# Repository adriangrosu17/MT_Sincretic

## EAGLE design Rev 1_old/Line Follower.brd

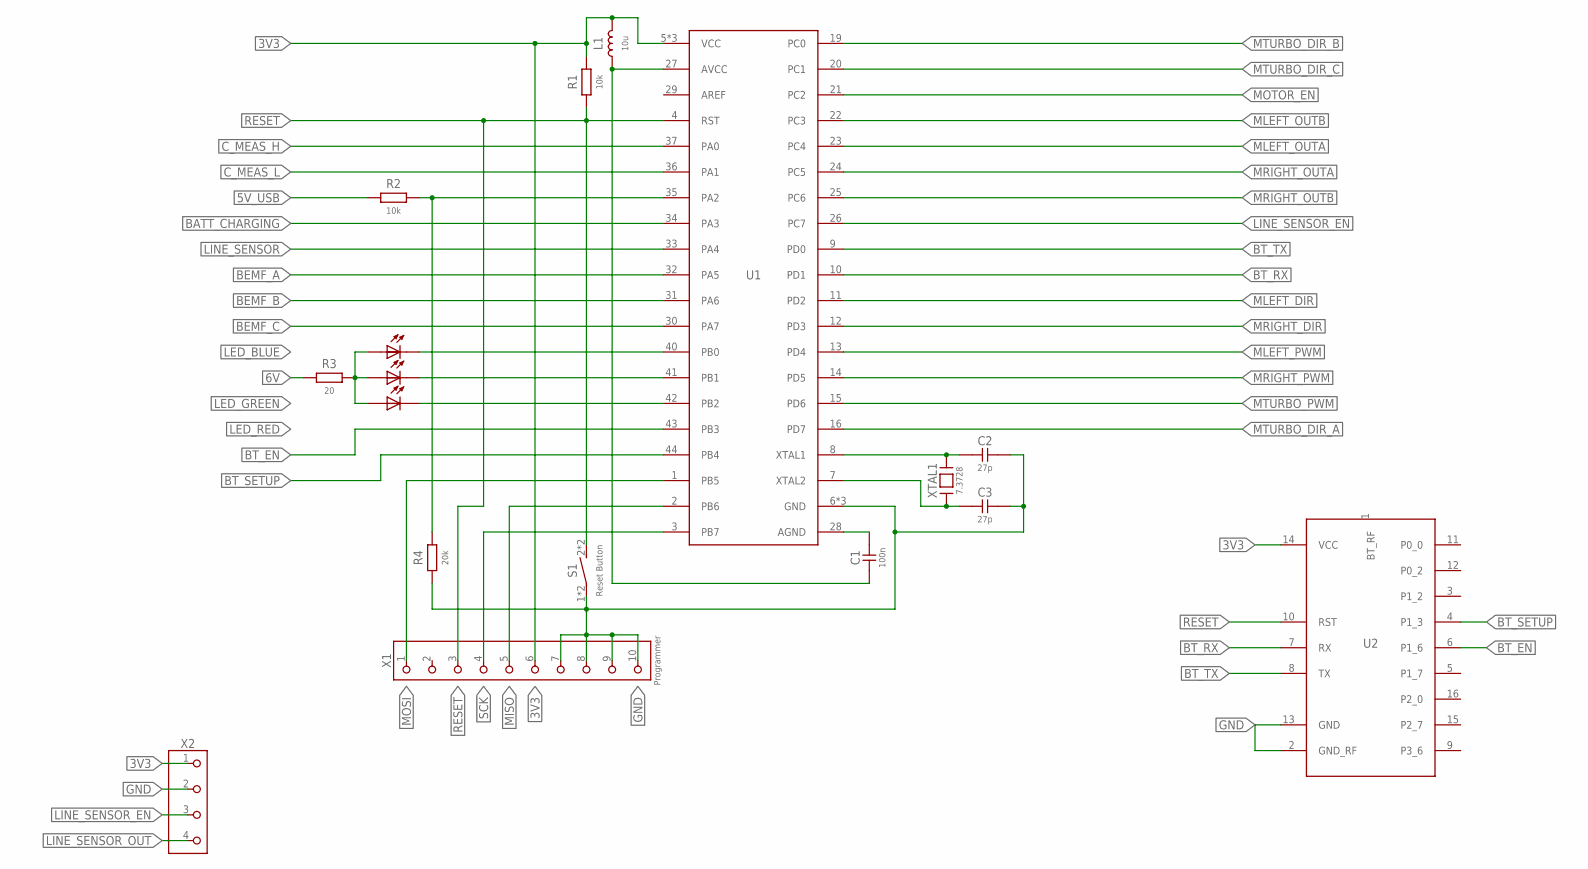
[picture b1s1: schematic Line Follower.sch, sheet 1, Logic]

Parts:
C1: 100n; SMD_1206
C2, C3: 27p; SMD_1206
D1: RGB_LEDOSTCXBSEC1E; OSTCXBSEC1E
L1: 10u; SMD_1206
R1, R2: 10k; SMD_1206
R3: 20; SMD_1206
R4: 20k; SMD_1206
S1: Reset Button; SCHURTER_BUTTON
U1: ATMEGA1284TQFP; TQFP-44
U2: RN4871
X1: Programmer; MALE_1WAY_2X5
X2: CONNECTOR_4PINMALE_PIN_1X4; MALE_PIN_1X4
XTAL1: 7.3728; SMD_OSCILLATOR

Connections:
3V3: L1.2, R1.2, U1.5 (VCC), U1.17 (VCC), U1.38 (VCC), U2.14 (VCC), X1.6, X2.1; also elsewhere on the board
5V_USB: R2.1; also elsewhere on the board
6V: R3.2; also elsewhere on the board
AVCC: C1.1, L1.1, U1.27 (AVCC)
BATT_CHARGING: U1.34 (PA3); also elsewhere on the board
BEMF_A: U1.32 (PA5); also elsewhere on the board
BEMF_B: U1.31 (PA6); also elsewhere on the board
BEMF_C: U1.30 (PA7); also elsewhere on the board
BT_EN: U1.43 (PB3), U2.6 (P1_6)
BT_RX: U1.10 (PD1), U2.7 (RX)
BT_SETUP: U1.44 (PB4), U2.4 (P1_3)
BT_TX: U1.9 (PD0), U2.8 (TX)
C_MEAS_H: U1.37 (PA0); also elsewhere on the board
C_MEAS_L: U1.36 (PA1); also elsewhere on the board
GND: C2.1, C3.1, R4.1, S1.1, S1.3, U1.6 (GND), U1.18 (GND), U1.39 (GND), U2.2 (GND_RF), U2.13 (GND), X1.7, X1.8, X1.9, X1.10, X2.2; also elsewhere on the board
LED_BLUE: D1.3 (K), U1.40 (PB0)
LED_GREEN: D1.1 (K), U1.41 (PB1)
LED_RED: D1.2 (K), U1.42 (PB2)
LINE_SENSOR: U1.33 (PA4)
LINE_SENSOR_EN: U1.26 (PC7), X2.3; also elsewhere on the board
LINE_SENSOR_OUT: X2.4; also elsewhere on the board
MISO: U1.2 (PB6), X1.5
MLEFT_DIR: U1.11 (PD2); also elsewhere on the board
MLEFT_OUTA: U1.23 (PC4); also elsewhere on the board
MLEFT_OUTB: U1.22 (PC3); also elsewhere on the board
MLEFT_PWM: U1.13 (PD4); also elsewhere on the board
MOSI: U1.1 (PB5), X1.1
MOTOR_EN: U1.21 (PC2); also elsewhere on the board
MRIGHT_DIR: U1.12 (PD3); also elsewhere on the board
MRIGHT_OUTA: U1.24 (PC5); also elsewhere on the board
MRIGHT_OUTB: U1.25 (PC6); also elsewhere on the board
MRIGHT_PWM: U1.14 (PD5); also elsewhere on the board
MTURBO_DIR_A: U1.16 (PD7); also elsewhere on the board
MTURBO_DIR_B: U1.19 (PC0); also elsewhere on the board
MTURBO_DIR_C: U1.20 (PC1); also elsewhere on the board
MTURBO_PWM: U1.15 (PD6); also elsewhere on the board
unnamed: C3.2, U1.7 (XTAL2), XTAL1.1
unnamed: C2.2, U1.8 (XTAL1), XTAL1.2
unnamed: C1.2, U1.28 (AGND)
unnamed: D1.4 (A), D1.5 (A), D1.6 (A), D1.PAD (A), R3.1
RESET: R1.1, S1.2 (S), S1.4 (S), U1.4 (RST), U2.10 (RST), X1.3
SCK: U1.3 (PB7), X1.4
USB_CONNECTED: R2.2, R4.2, U1.35 (PA2)

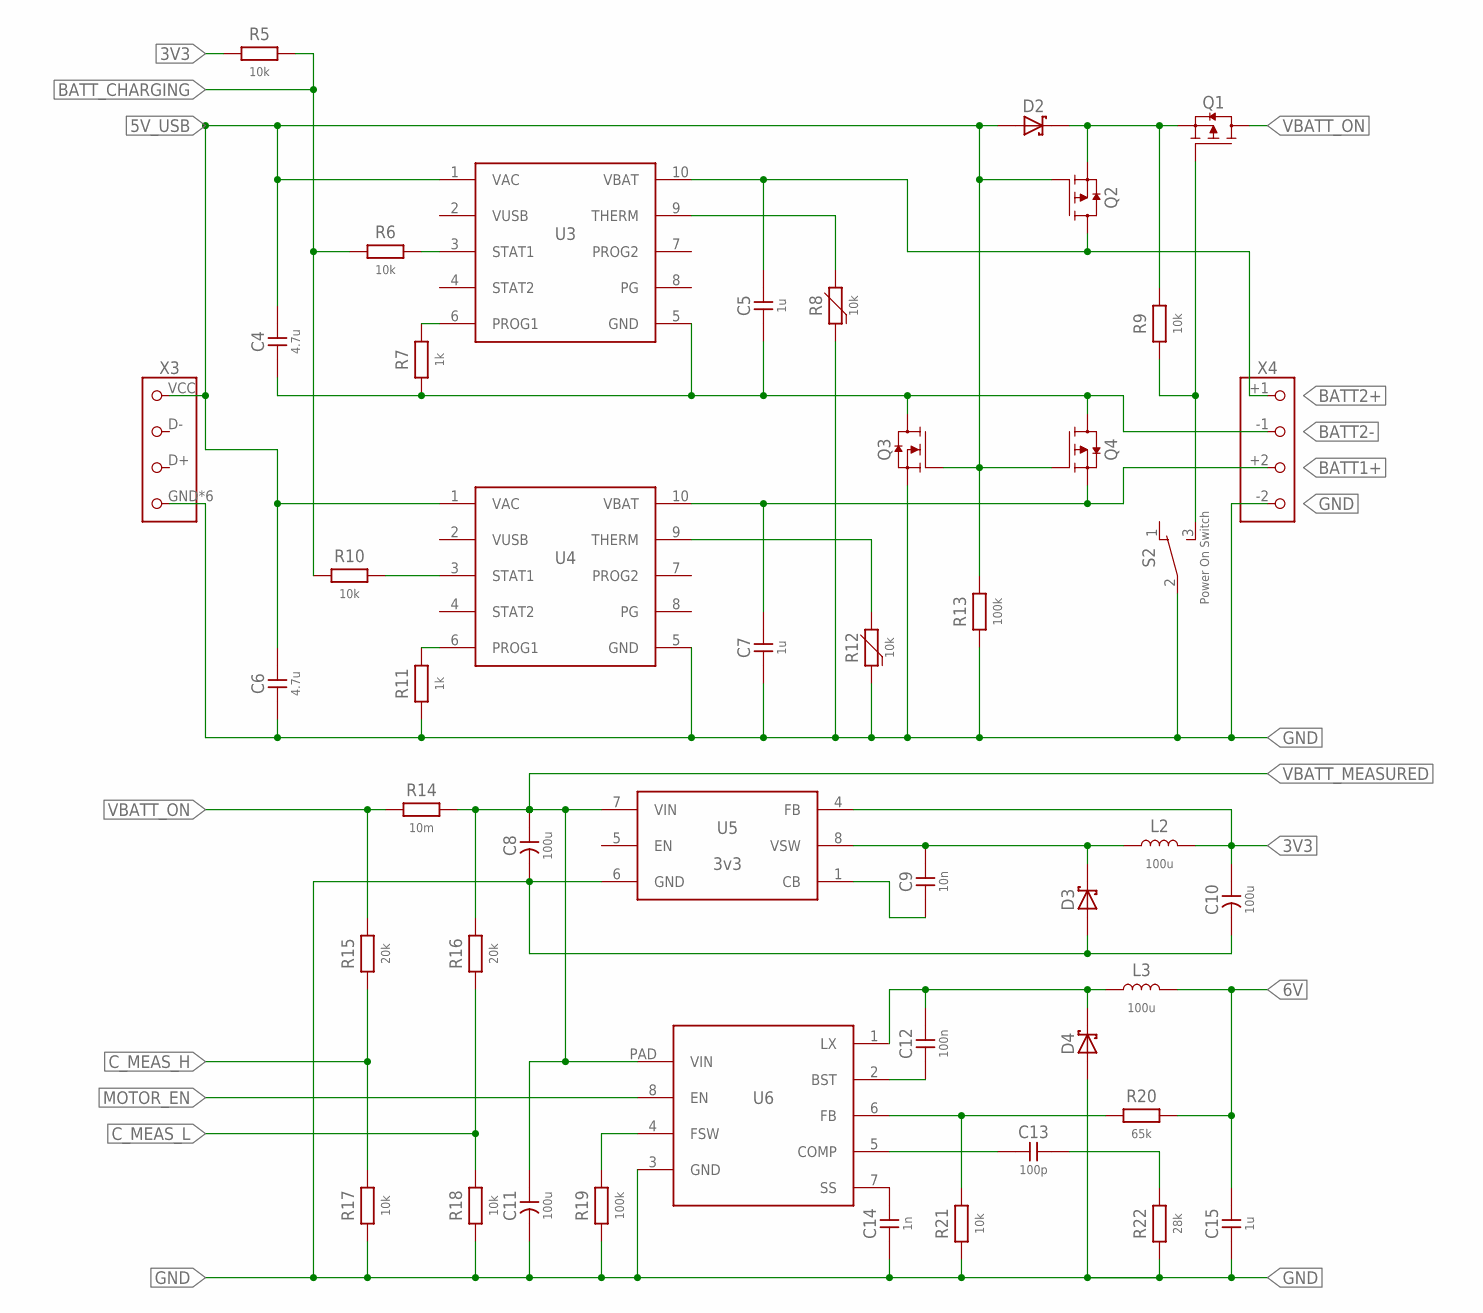
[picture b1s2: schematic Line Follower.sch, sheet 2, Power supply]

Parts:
C4, C6: 4.7u; SMD_1206
C5, C7, C15: 1u; SMD_1206
C8, C10, C11: 100u; SMD_1210
C9: 10n; SMD_1206
C12: 100n; SMD_1206
C13: 100p; SMD_1206
C14: 1n; SMD_1206
D2, D3, D4: BAS3010BSOD232; SOD323
L2, L3: 100u; SMD_1206
Q1, Q2, Q4: AOD417; TO-252
Q3: AOD480; TO-252
R5, R6, R9, R10, R17, R18, R21: 10k; SMD_1206
R7, R11: 1k; SMD_1206
R8, R12: 10k; SMD_0805
R13, R19: 100k; SMD_1206
R14: 10m; SMD_1206
R15, R16: 20k; SMD_1206
R20: 65k; SMD_1206
R22: 28k; SMD_1206
S2: Power On Switch; NINIGI_5MS1
U3, U4: MCP73837MSOP_10; MSOP_10
U5: 3v3; SO8
U6: AOZ1284; SO8_EP
X3: USB_CONNECTORMICRO_USB; MICRO_USB_FEMALE
X4: CONNECTOR_4PINBATTERY_18650X2; BATTERY_186501X2

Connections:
3V3: C10.1 (+), L2.2, R5.1, U5.4 (FB); also elsewhere on the board
5V_USB: C4.2, C6.2, D2.1 (A), Q2.1 (G), Q3.1 (G), Q4.1 (G), R13.2, U3.1 (VAC), U4.1 (VAC), X3.VCC (1); also elsewhere on the board
6V: C15.2, L3.2, R20.2; also elsewhere on the board
BATT1+: C7.2, Q4.2 (S), U4.10 (VBAT), X4.+2 (3)
BATT2+: C5.2, Q2.3 (D), U3.10 (VBAT), X4.+1 (1)
BATT2-: C4.1, C5.1, Q3.3 (D), Q4.3 (D), R7.1, U3.5 (GND), X4.-1 (2)
BATTERY1_CHARGING1: R10.2, U4.3 (STAT1)
BATTERY2_CHARGING1: R6.2, U3.3 (STAT1)
BATT_CHARGING: R5.2, R6.1, R10.1; also elsewhere on the board
C_MEAS_H: R15.1, R17.2; also elsewhere on the board
C_MEAS_L: R16.1, R18.2; also elsewhere on the board
GND: C6.1, C7.1, C8.2 (-), C10.2 (-), C11.2 (-), C14.1, C15.1, D3.1 (A), D4.1 (A), Q3.2 (S), R8.1, R11.1, R12.1, R13.1, R17.1, R18.1, R19.1, R21.1, R22.1, S2.2 (MIDDLE), U4.5 (GND), U5.6 (GND), U6.3 (GND), X3.GND (4), X3.NC (4), X3.NC@2 (4), X3.NC@3 (4), X3.NC@4 (4), X3.NC@5 (4), X4.-2 (4); also elsewhere on the board
MOTOR_EN: U6.8 (EN); also elsewhere on the board
unnamed: C9.1, U5.1 (CB)
unnamed: R19.2, U6.4 (FSW)
unnamed: C14.2, U6.7 (SS)
unnamed: C13.1, U6.5 (COMP)
unnamed: C13.2, R22.2
unnamed: C12.1, U6.2 (BST)
unnamed: C12.2, D4.2 (K), L3.1, U6.1 (LX)
unnamed: R20.1, R21.2, U6.6 (FB)
THERM2: R12.2, U4.9 (THERM)
THERM3: R8.2, U3.9 (THERM)
VBATT1: D2.2 (K), Q1.2 (S), Q2.2 (S), R9.2
VBATT_MEASURED: C8.1 (+), C11.1 (+), R14.2, R16.2, U5.7 (VIN), U6.PAD (VIN); also elsewhere on the board
VBATT_ON: Q1.3 (D), R14.1, R15.2
VG1: Q1.1 (G), R9.1, S2.3 (SIDE2)
VSW: C9.2, D3.2 (K), L2.1, U5.8 (VSW)
VUSB: U3.2 (VUSB), U4.2 (VUSB)
V_LIMIT2: R11.2, U4.6 (PROG1)
V_LIMIT3: R7.2, U3.6 (PROG1)

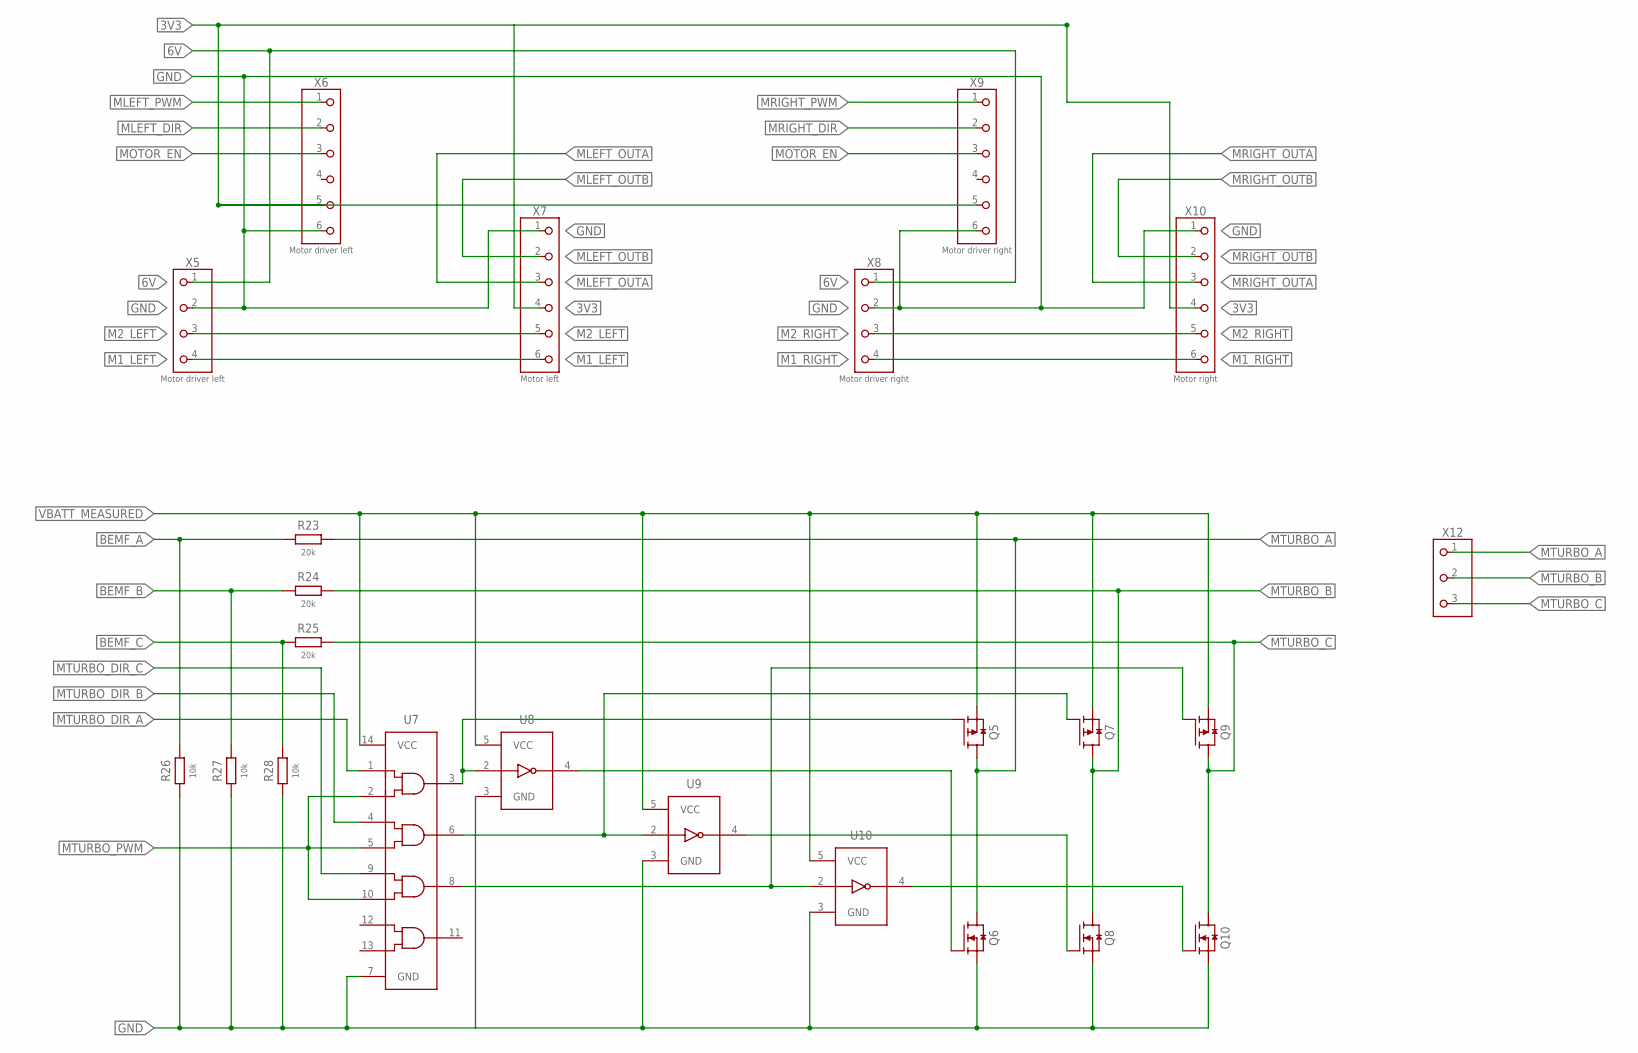
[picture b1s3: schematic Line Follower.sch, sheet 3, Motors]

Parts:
Q5, Q7, Q9: AOD417; TO-252
Q6, Q8, Q10: AOD480; TO-252
R23, R24, R25: 20k; SMD_1206
R26, R27, R28: 10k; SMD_1206
U7: 74AHC08D; SO14
U8, U9, U10: 74LVC1G14SOT25; SOT25
X5: Motor driver left; MALE_PIN_1X4
X6: Motor driver left; MALE_PIN_1X6
X7: Motor left; MALE_PIN_2X3
X8: Motor driver right; MALE_PIN_1X4
X9: Motor driver right; MALE_PIN_1X6
X10: Motor right; MALE_PIN_2X3
X12: CONNECTOR_3PIN; SCREW_1X3

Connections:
3V3: X6.5, X7.4, X9.5, X10.4; also elsewhere on the board
6V: X5.1, X8.1; also elsewhere on the board
BEMF_A: R23.1, R26.2; also elsewhere on the board
BEMF_B: R24.1, R27.2; also elsewhere on the board
BEMF_C: R25.1, R28.2; also elsewhere on the board
GND: Q6.2 (S), Q8.2 (S), Q10.2 (S), R26.1, R27.1, R28.1, U7.7 (GND), U8.3 (GND), U9.3 (GND), U10.3 (GND), X5.2, X6.6, X7.1, X8.2, X9.6, X10.1; also elsewhere on the board
M1_LEFT: X5.4, X7.6
M1_RIGHT: X8.4, X10.6
M2_LEFT: X5.3, X7.5
M2_RIGHT: X8.3, X10.5
MLEFT_DIR: X6.2; also elsewhere on the board
MLEFT_OUTA: X7.3; also elsewhere on the board
MLEFT_OUTB: X7.2; also elsewhere on the board
MLEFT_PWM: X6.1; also elsewhere on the board
MOTOR_EN: X6.3, X9.3; also elsewhere on the board
MRIGHT_DIR: X9.2; also elsewhere on the board
MRIGHT_OUTA: X10.3; also elsewhere on the board
MRIGHT_OUTB: X10.2; also elsewhere on the board
MRIGHT_PWM: X9.1; also elsewhere on the board
MTURBO_A: Q5.3 (D), Q6.3 (D), R23.2, X12.1
MTURBO_B: Q7.3 (D), Q8.3 (D), R24.2, X12.2
MTURBO_C: Q9.3 (D), Q10.3 (D), R25.2, X12.3
MTURBO_DIR_A: U7.1 (A1); also elsewhere on the board
MTURBO_DIR_B: U7.4 (A2); also elsewhere on the board
MTURBO_DIR_C: U7.9 (A3); also elsewhere on the board
MTURBO_PWM: U7.2 (B1), U7.5 (B2), U7.10 (B3); also elsewhere on the board
unnamed: Q5.1 (G), U7.3 (Y1), U8.2 (A)
unnamed: Q6.1 (G), U8.4 (Y)
unnamed: Q7.1 (G), U7.6 (Y2), U9.2 (A)
unnamed: Q8.1 (G), U9.4 (Y)
unnamed: Q10.1 (G), U10.4 (Y)
unnamed: Q9.1 (G), U7.8 (Y3), U10.2 (A)
VBATT_MEASURED: Q5.2 (S), Q7.2 (S), Q9.2 (S), U7.14 (VCC), U8.5 (VCC), U9.5 (VCC), U10.5 (VCC); also elsewhere on the board

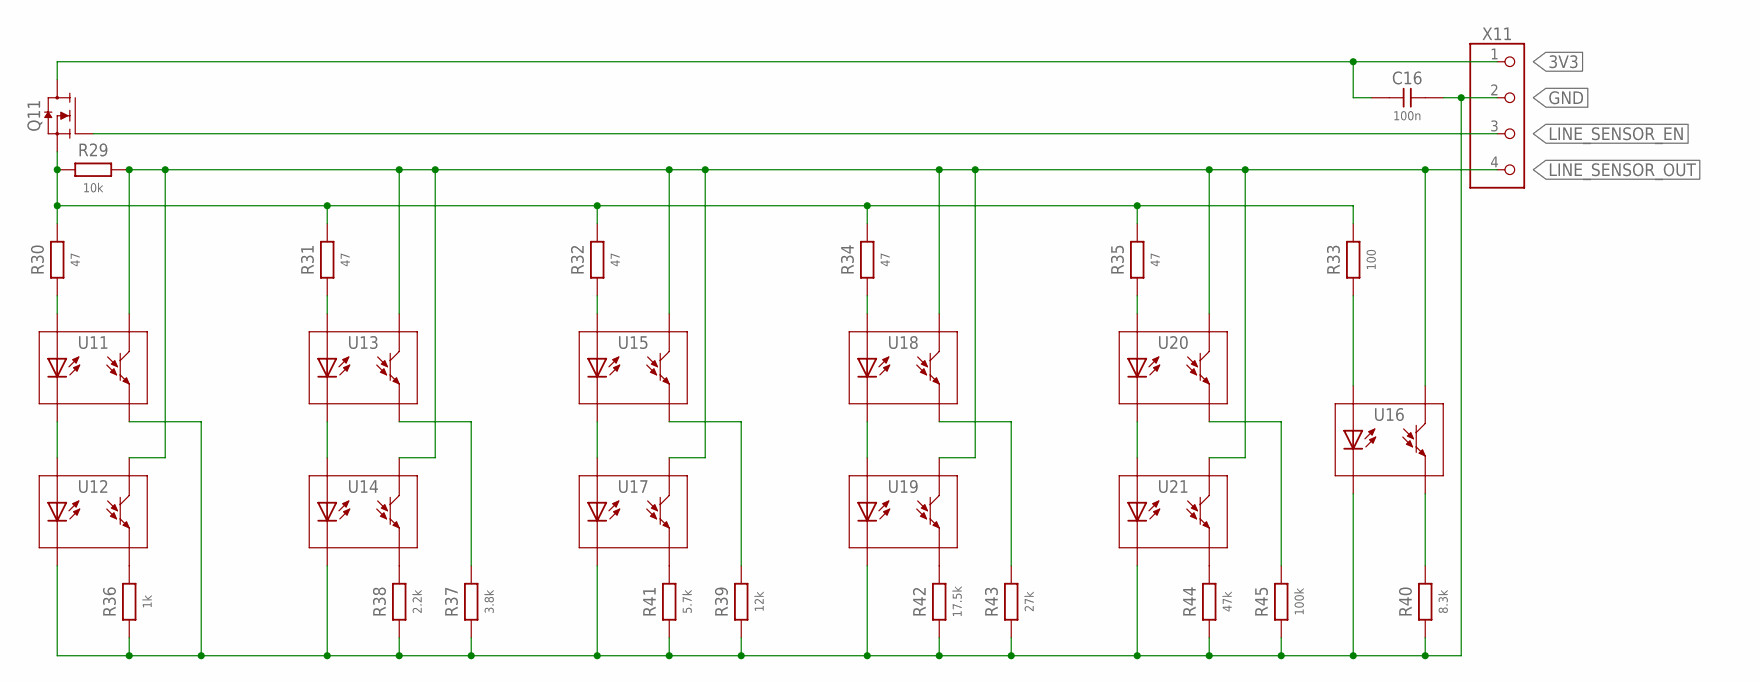
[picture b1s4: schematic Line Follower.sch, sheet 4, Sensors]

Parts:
C16: 100n; SMD_1206
Q11: AO3414SOT23; SOT23
R29: 10k; SMD_1206
R30, R31, R32, R34, R35: 47; SMD_1206
R33: 100; SMD_1206
R36: 1k; SMD_1206
R37: 3.8k; SMD_1206
R38: 2.2k; SMD_1206
R39: 12k; SMD_1206
R40: 8.3k; SMD_1206
R41: 5.7k; SMD_1206
R42: 17.5k; SMD_1206
R43: 27k; SMD_1206
R44: 47k; SMD_1206
R45: 100k; SMD_1206
U11, U12, U13, U14, U15, U16, U17, U18, U19, U20, U21: EE-SY171
X11: CONNECTOR_4PINMALE_PIN_1X4; MALE_PIN_1X4

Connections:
3V3: C16.1, Q11.3 (D), X11.1; also elsewhere on the board
3V3_SENSOR_LEDS: Q11.2 (S), R29.1, R30.2, R31.2, R32.2, R33.2, R34.2, R35.2
GND: C16.2, R36.1, R37.1, R38.1, R39.1, R40.1, R41.1, R42.1, R43.1, R44.1, R45.1, U11.E, U12.K, U14.K, U16.K, U17.K, U19.K, U21.K, X11.2; also elsewhere on the board
LINE_SENSOR_EN: Q11.1 (G), X11.3; also elsewhere on the board
LINE_SENSOR_OUT: R29.2, U11.C, U12.C, U13.C, U14.C, U15.C, U16.C, U17.C, U18.C, U19.C, U20.C, U21.C, X11.4; also elsewhere on the board
unnamed: R36.2, U12.E
unnamed: R37.2, U13.E
unnamed: R30.1, U11.A
unnamed: U11.K, U12.A
unnamed: R32.1, U15.A
unnamed: R31.1, U13.A
unnamed: U13.K, U14.A
unnamed: U15.K, U17.A
unnamed: R34.1, U18.A
unnamed: U18.K, U19.A
unnamed: R35.1, U20.A
unnamed: U20.K, U21.A
unnamed: R33.1, U16.A
unnamed: R38.2, U14.E
unnamed: R41.2, U17.E
unnamed: R39.2, U15.E
unnamed: R43.2, U18.E
unnamed: R42.2, U19.E
unnamed: R45.2, U20.E
unnamed: R44.2, U21.E
unnamed: R40.2, U16.E

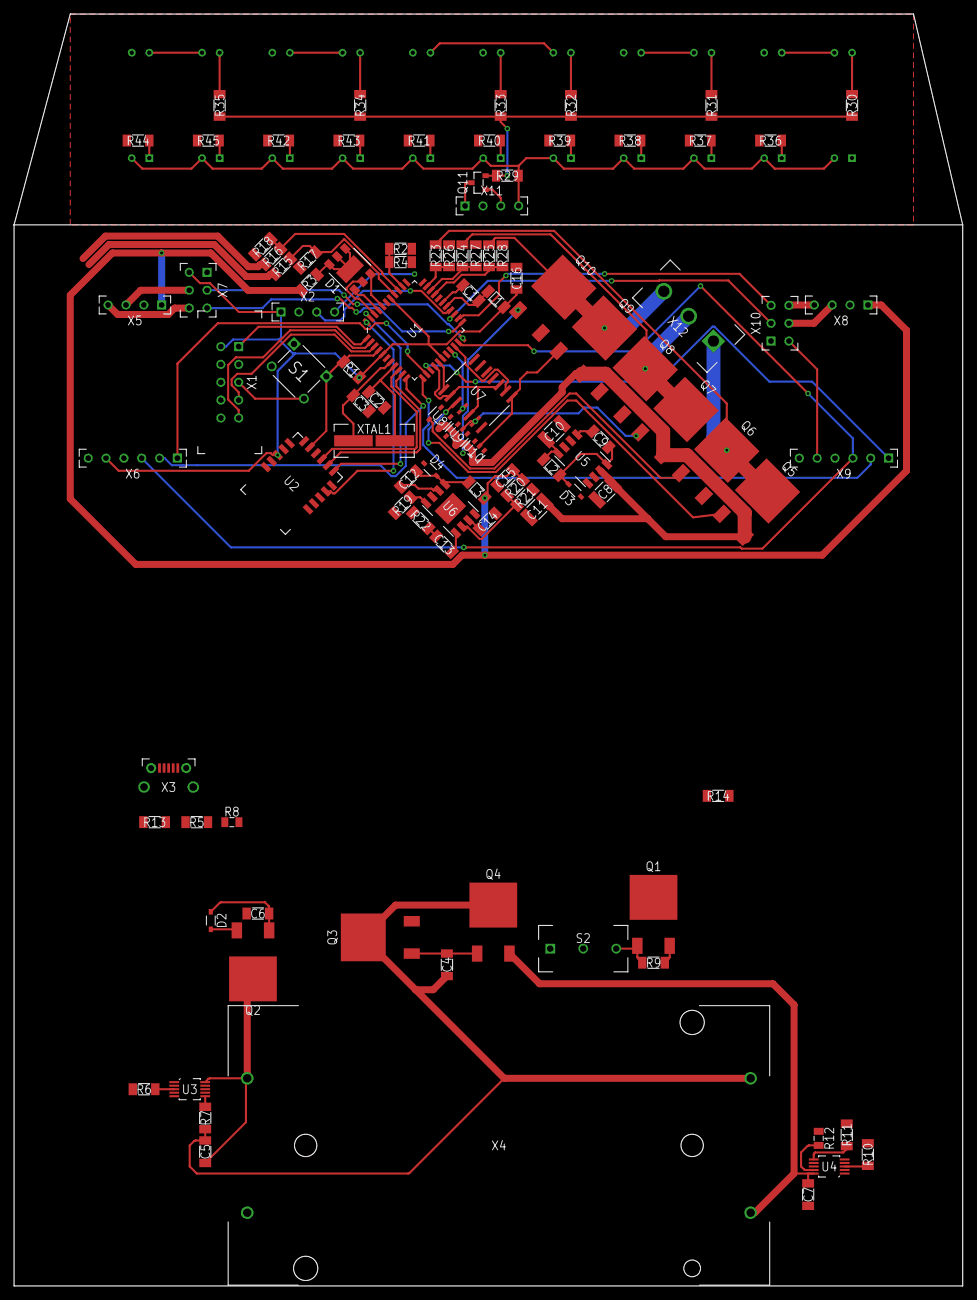
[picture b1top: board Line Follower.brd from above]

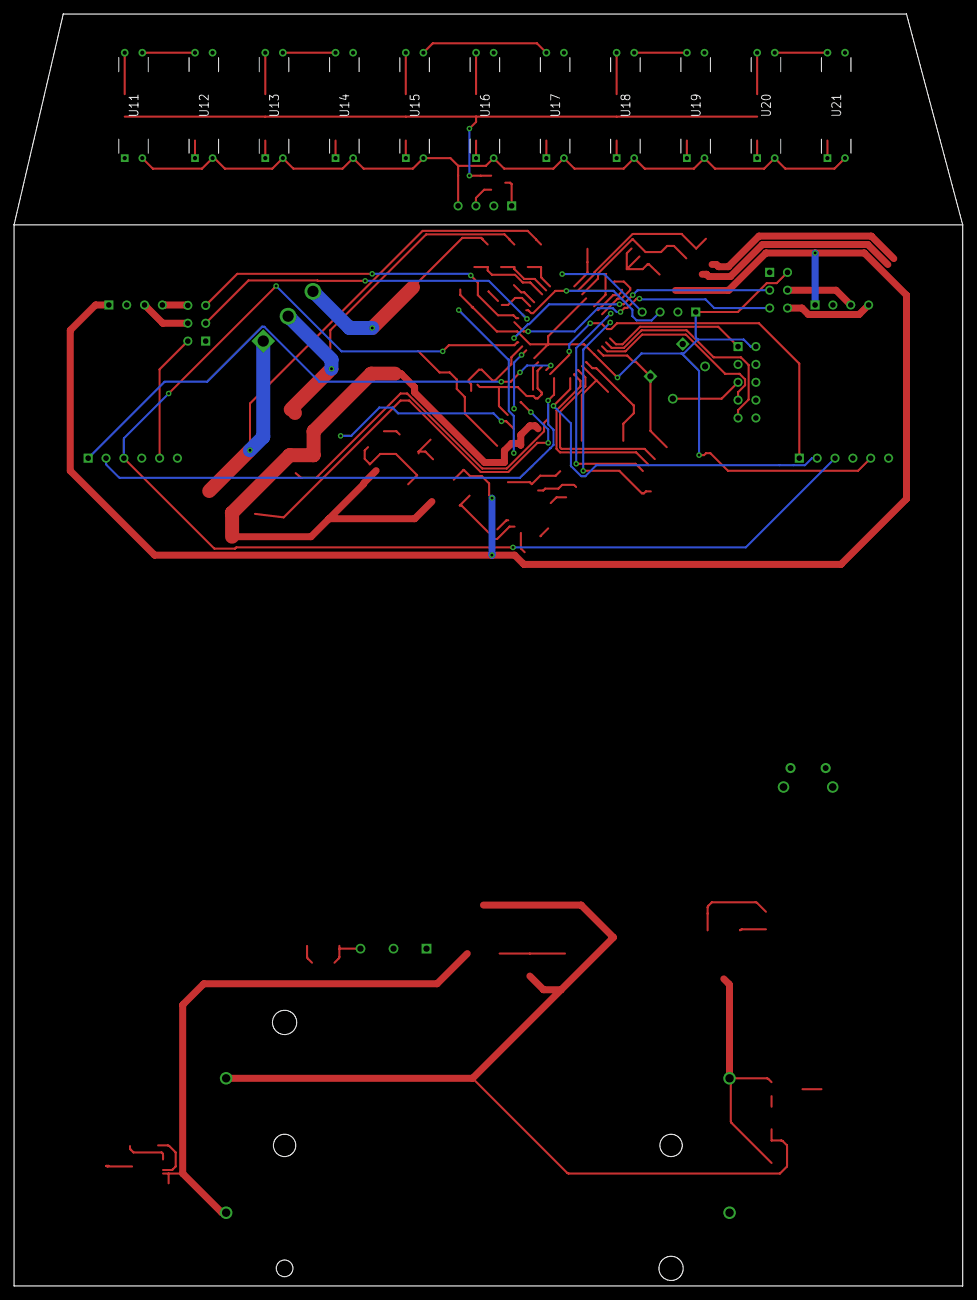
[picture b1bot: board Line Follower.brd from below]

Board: 2 copper layers, 135.0 x 181.0 mm, 115 parts (11 on the bottom side), 100 nets.

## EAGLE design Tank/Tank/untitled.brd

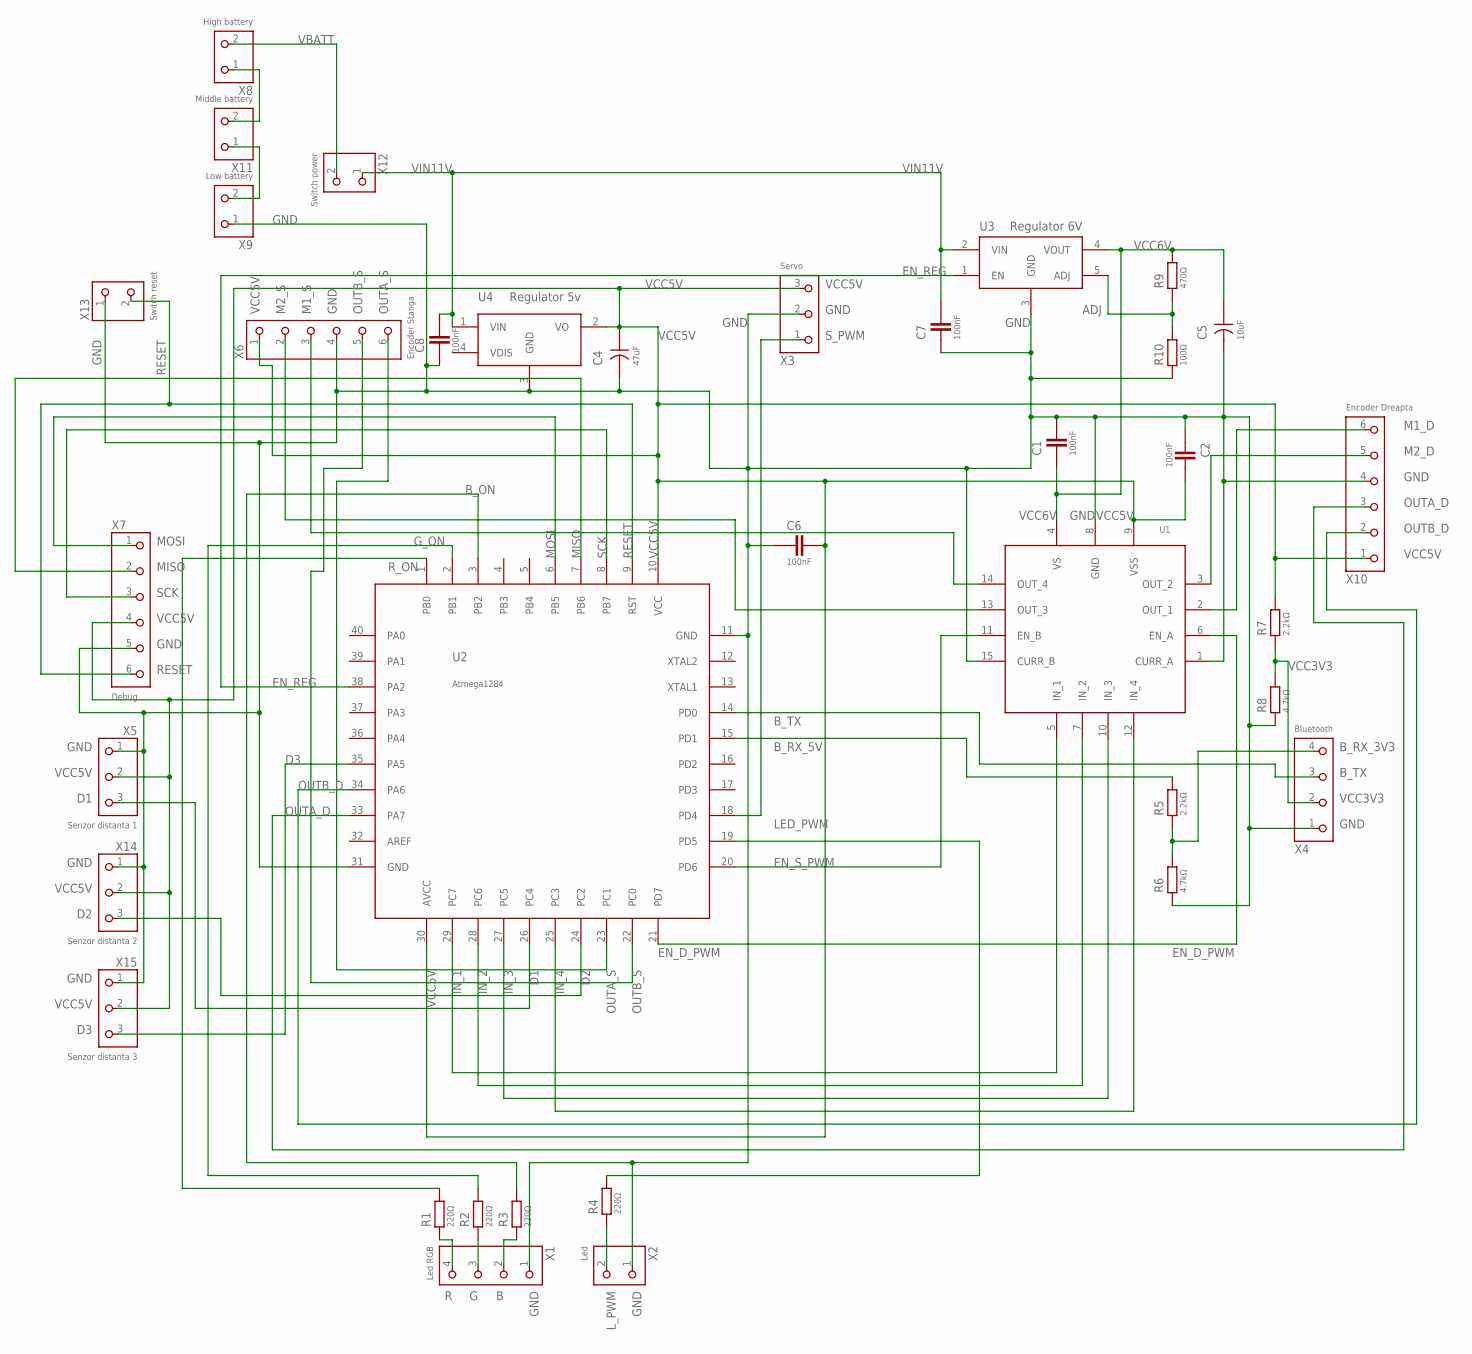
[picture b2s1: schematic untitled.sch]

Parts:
C1, C2, C6, C7, C8: 100nF; THT_2.54
C4: 47uF; ELECTROLYTIC_5MM_PEFRBOARD
C5: 10uF; ELECTROLYTIC_5MM_PEFRBOARD
R1, R2, R3, R4: 220Ω; THT_5.08
R5: 2.2kΩ; THT_2.54
R6, R8: 4.7kΩ; THT_5.08
R7: 2.2kΩ; THT_5.08
R9: 470Ω; THT_2.54
R10: 100Ω; THT_5.08
U1: L298NMULTIWATT15V_PERFBOARD; MULTIWATT15V_PERFBOARD
U2: Atmega1284; DIP-40
U3: Regulator 6V; TO-220-5_PERFBOARD
U4: Regulator 5v; TO-220-4
X1: Led RGB; MALE_PIN_1X4
X2: Led; MALE_PIN_1X2
X3: Servo; MALE_PIN_1X3
X4: Bluetooth; MALE_PIN_1X4
X5: Senzor distanta 1; MALE_PIN_1X3
X6: Encoder Stanga; MALE_PIN_2X3
X7: Debug; MALE_PIN_2X3
X8: High battery; FEMALE_SCREW_1X2
X9: Low battery; FEMALE_SCREW_1X2
X10: Encoder Dreapta; MALE_PIN_2X3
X11: Middle battery; FEMALE_SCREW_1X2
X12: Switch power; MALE_PIN_1X2
X13: Switch reset; MALE_PIN_1X2
X14: Senzor distanta 2; MALE_PIN_1X3
X15: Senzor distanta 3; MALE_PIN_1X3

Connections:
ADJ: R9.1, R10.2, U3.5 (ADJ)
B: R3.1, X1.2
B_ON: R3.2, U2.3 (PB2)
B_RX_3V3: R5.1, R6.2, X4.4
B_RX_5V: R5.2, U2.15 (PD1)
B_TX: U2.14 (PD0), X4.3
D1: U2.26 (PC4), X5.3
D2: U2.24 (PC2), X14.3
D3: U2.35 (PA5), X15.3
EN_D_PWM: U1.6 (EN_A), U2.21 (PD7)
EN_REG: U2.38 (PA2), U3.1 (EN)
EN_S_PWM: U1.11 (EN_B), U2.20 (PD6)
G: R2.1, X1.3
GND: C1.2, C2.1, C4.-, C5.-, C6.1, C7.1, C8.1, R6.1, R8.1, R10.1, U1.1 (CURR_A), U1.8 (GND), U1.15 (CURR_B), U2.11 (GND), U2.31 (GND), U3.3 (GND), U4.3 (GND), X1.1, X2.1, X3.2, X4.1, X5.1, X6.4, X7.5, X9.1, X10.4, X13.1, X14.1, X15.1
G_ON: R2.2, U2.2 (PB1)
IN_1: U1.5 (IN_1), U2.29 (PC7)
IN_2: U1.7 (IN_2), U2.28 (PC6)
IN_3: U1.10 (IN_3), U2.27 (PC5)
IN_4: U1.12 (IN_4), U2.25 (PC3)
LED_PWM: R4.2, U2.19 (PD5)
L_PWM: R4.1, X2.2
M1_D: U1.2 (OUT_1), X10.6
M1_S: U1.14 (OUT_4), X6.3
M2_D: U1.3 (OUT_2), X10.5
M2_S: U1.13 (OUT_3), X6.2
MISO: U2.7 (PB6), X7.2
MOSI: U2.6 (PB5), X7.1
unnamed: X8.1, X11.2
unnamed: X9.2, X11.1
OUTA_D: U2.33 (PA7), X10.3
OUTA_S: U2.23 (PC1), X6.6
OUTB_D: U2.34 (PA6), X10.2
OUTB_S: U2.22 (PC0), X6.5
R: R1.1, X1.4
RESET: U2.9 (RST), X7.6, X13.2
R_ON: R1.2, U2.1 (PB0)
SCK: U2.8 (PB7), X7.3
S_PWM: U2.18 (PD4), X3.1
VBATT: X8.2, X12.2
VCC3V3: R7.1, R8.2, X4.2
VCC5V: C2.2, C4.+, C6.2, R7.2, U1.9 (VSS), U2.10 (VCC), U2.30 (AVCC), U4.2 (VO), X3.3, X5.2, X6.1, X7.4, X10.1, X14.2, X15.2
VCC6V: C1.1, C5.+, R9.2, U1.4 (VS), U3.4 (VOUT)
VIN11V: C7.2, C8.2, U3.2 (VIN), U4.1 (VIN), X12.1

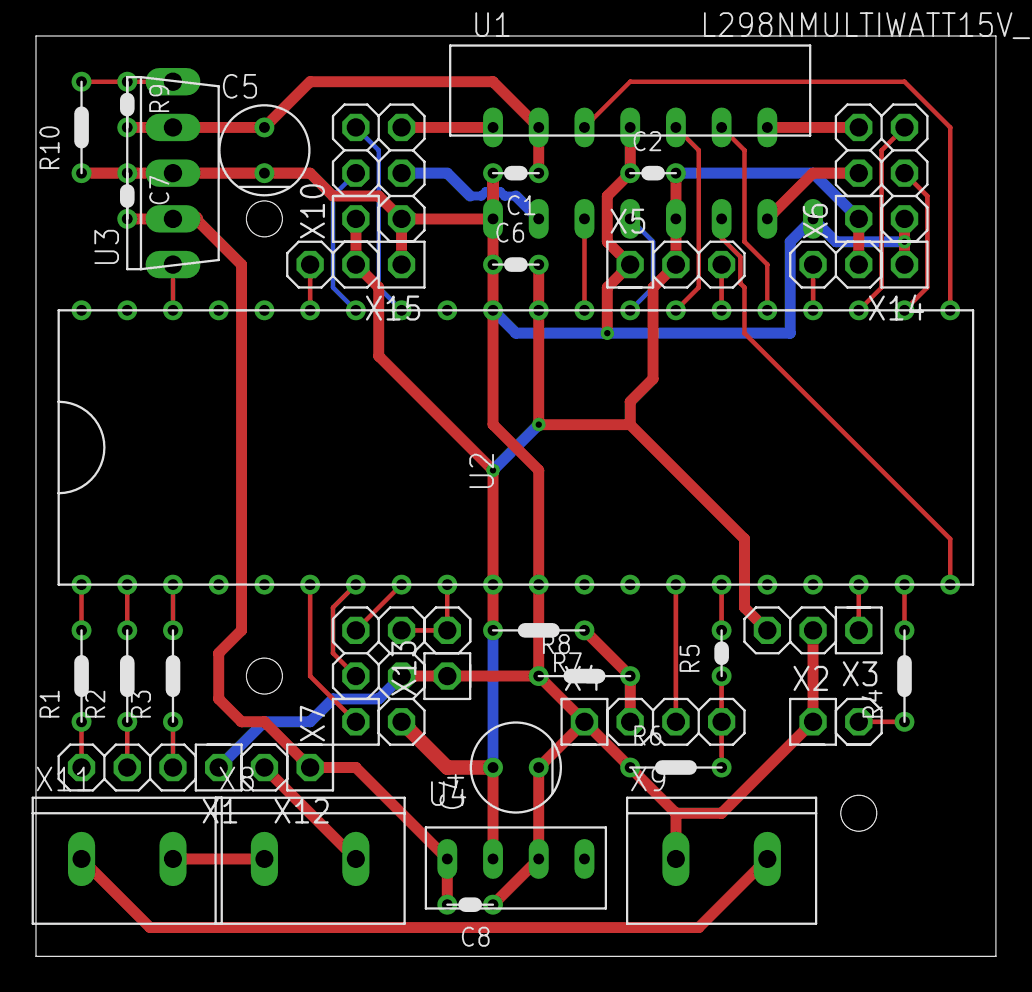
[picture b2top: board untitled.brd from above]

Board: 2 copper layers, 53.3 x 51.1 mm, 36 parts (0 on the bottom side), 43 nets.

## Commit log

2017-10-25 ADC/PWM
    added adc.h/adc.c
    added pwm.h/pwm.c
2017-10-31 pwm/gpio
    fixed pwm bugs
    added gpio
2017-11-07 UART
    Added UART implementation
2017-11-20 Electronic layout/schematic added
    Added the electronic schematic and board layout (built in Eagle)
2018-01-01 laptop->pc test part
2018-01-05 motors+encoder+uart_interrupt
2018-01-06 final push
2018-01-08 Added pictures and videos
2018-03-05 encoders+sensor
2018-03-05 robot 95% done
2018-03-30 project done
2018-04-20 started working with eeprom
2018-04-20 buffer for uart receive
2018-05-29 finished sem 2 project
2018-07-26 teijsiadjsai
2018-07-26 fajdosadjas
